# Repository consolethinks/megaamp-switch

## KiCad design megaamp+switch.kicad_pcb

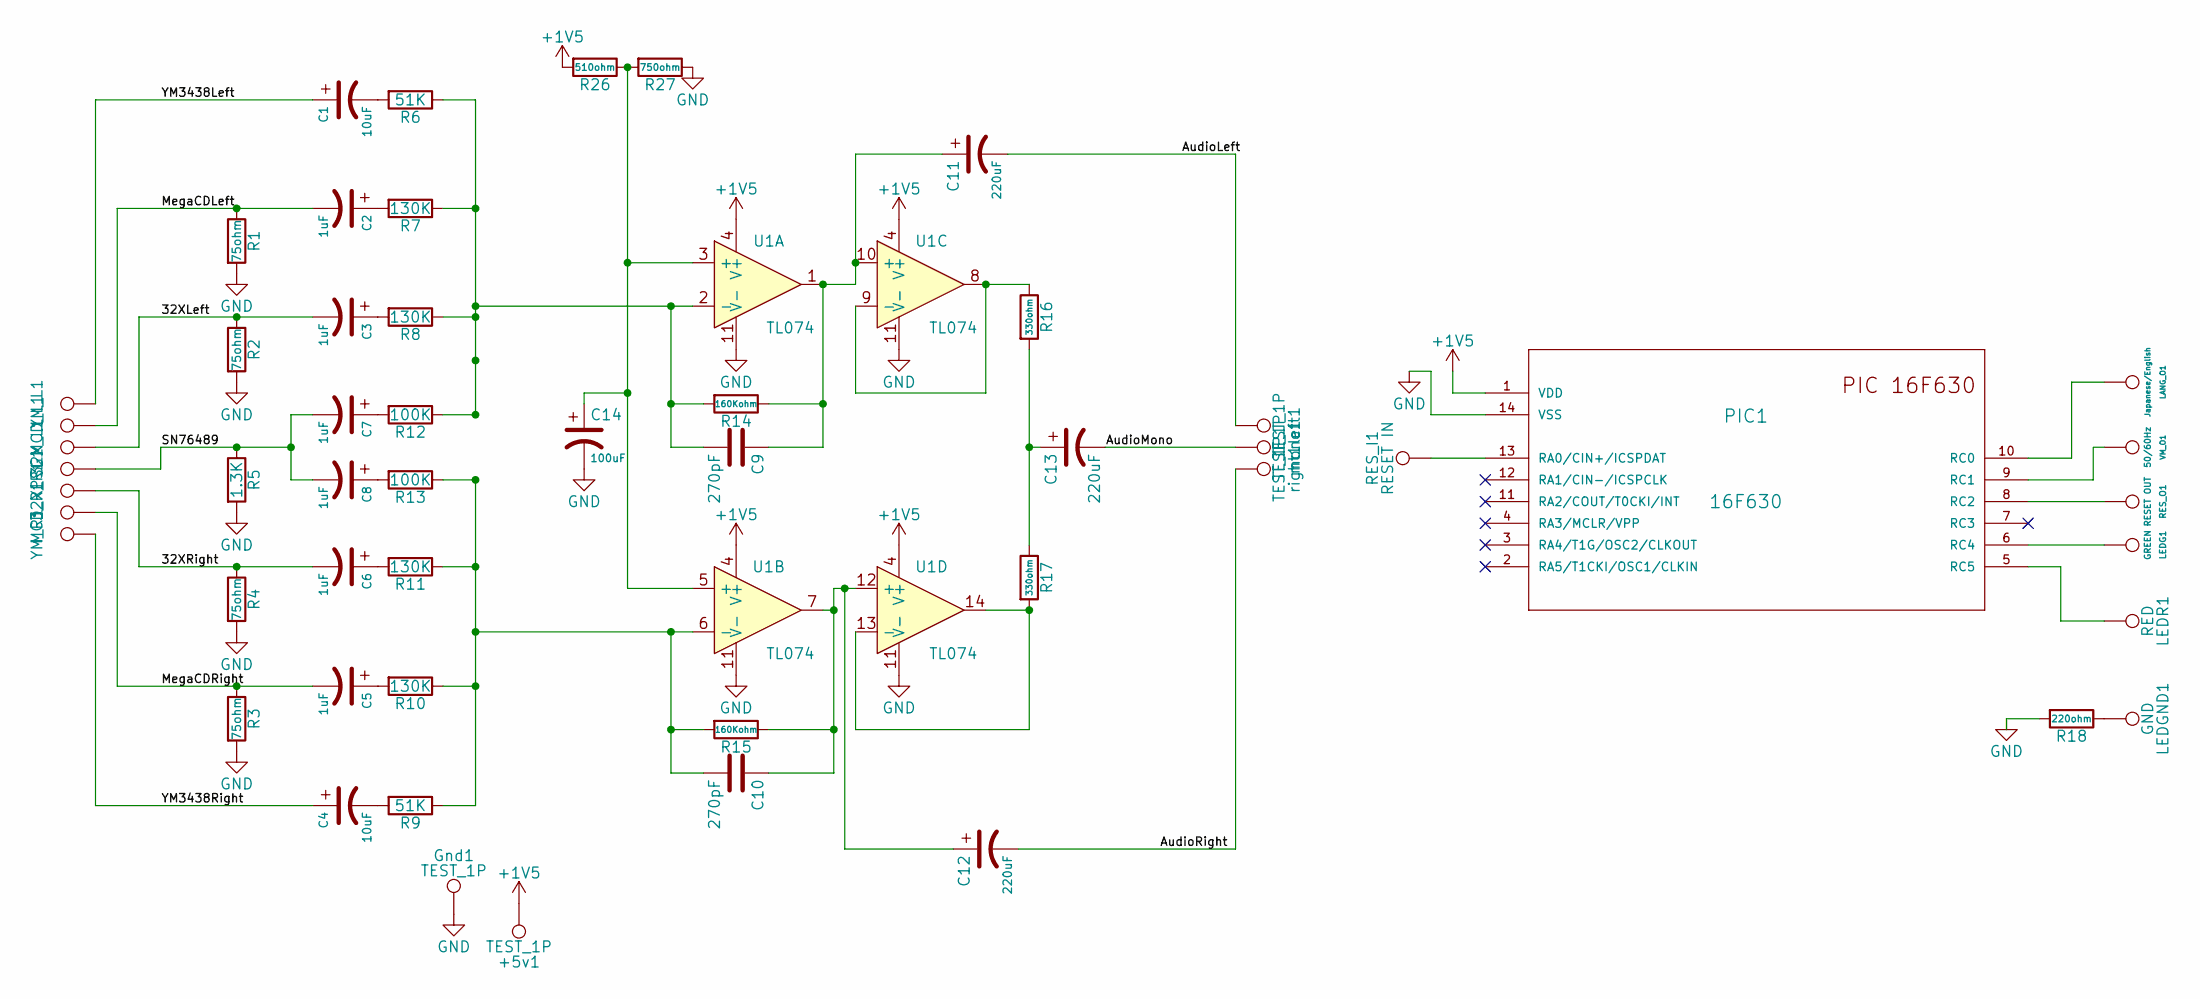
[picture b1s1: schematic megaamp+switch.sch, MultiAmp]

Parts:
32X_L1: 32X Left Channel; SolderWirePad_single_0-8mmDrill
32X_R1: 32X Right Channel; SolderWirePad_single_0-8mmDrill
+5v1: TEST_1P; SolderWirePad_single_0-8mmDrill
C1, C4: 10uF; c_elec_4x5.3
C2, C3, C5, C6, C7, C8: 1uF; c_elec_4x5.3
C9, C10: 270pF; C_Disc_D7.5_P5
C11, C12, C13: 220uF; c_elec_4x5.3
C14: 100uF; c_elec_4x5.3
Gnd1: TEST_1P; SolderWirePad_single_0-8mmDrill
LANG_O1: Japanese/English; SolderWirePad_single_0-8mmDrill
LEDG1: GREEN; SolderWirePad_single_0-8mmDrill
LEDGND1: GND; SolderWirePad_single_0-8mmDrill
LEDR1: RED; SolderWirePad_single_0-8mmDrill
MCD_L1: Mega CD Left Channel; SolderWirePad_single_0-8mmDrill
MCD_R1: Mega CD Right Channel; SolderWirePad_single_0-8mmDrill
PIC1: 16F630; DIP-14_W7.62mm
PSG1: PSG; SolderWirePad_single_0-8mmDrill
R1, R2, R3, R4: 75ohm; R_1206
R5: 1.3K; R_1206
R6, R9: 51K; R_1206
R7, R8, R10, R11: 130K; R_1206
R12, R13: 100K; R_1206
R14, R15: 160Kohm; R_1206
R16, R17: 330ohm; R_1206
R18: 220ohm; R_1206
R26: 510ohm; R_1206
R27: 750ohm; R_1206
RES_I1: RESET IN; SolderWirePad_single_0-8mmDrill
RES_O1: RESET OUT; SolderWirePad_single_0-8mmDrill
U1: TL074; SOIC-14_N
VM_O1: 50/60Hz; SolderWirePad_single_0-8mmDrill
YM_L1: Yamaha left channel; SolderWirePad_single_0-8mmDrill
YM_R1: Yamaha Right Channel; SolderWirePad_single_0-8mmDrill
left1: TEST_1P; SolderWirePad_single_0-8mmDrill
mono1: TEST_1P; SolderWirePad_single_0-8mmDrill
right1: TEST_1P; SolderWirePad_single_0-8mmDrill

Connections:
+1V5: +5v1.1, PIC1.1 (VDD), R26.2, U1.4 (V+)
/32XLeft: 32X_L1.1, C3.2, R2.1
/32XRight: 32X_R1.1, C6.2, R4.1
/AudioLeft: C11.2, left1.1
/AudioMono: C13.2, mono1.1
/AudioRight: C12.2, right1.1
/MegaCDLeft: C2.2, MCD_L1.1, R1.1
/MegaCDRight: C5.2, MCD_R1.1, R3.1
/SN76489: C7.2, C8.2, PSG1.1, R5.1
/YM3438Left: C1.1, YM_L1.1
/YM3438Right: C4.1, YM_R1.1
GND: C14.2, Gnd1.1, PIC1.14 (VSS), R1.2, R2.2, R3.2, R4.2, R5.2, R18.2, R27.1, U1.11 (V-)
unnamed: C1.2, R6.2
unnamed: C2.1, R7.2
unnamed: C3.1, R8.2
unnamed: C4.2, R9.2
unnamed: C5.1, R10.2
unnamed: C6.1, R11.2
unnamed: C7.1, R12.2
unnamed: C8.1, R13.2
unnamed: C9.2, R6.1, R7.1, R8.1, R12.1, R14.2, U1.2 (-)
unnamed: C10.1, C12.1, R15.1, U1.7, U1.12 (+)
unnamed: C10.2, R9.1, R10.1, R11.1, R13.1, R15.2, U1.6 (-)
unnamed: C9.1, C11.1, R14.1, U1.1, U1.10 (+)
unnamed: C13.1, R16.2, R17.1
unnamed: C14.1, R26.1, R27.2, U1.3 (+), U1.5 (+)
unnamed: LANG_O1.1, PIC1.10 (RC0)
unnamed: LEDG1.1, PIC1.6 (RC4)
unnamed: LEDGND1.1, R18.1
unnamed: LEDR1.1, PIC1.5 (RC5)
unnamed: PIC1.8 (RC2), RES_O1.1
unnamed: PIC1.9 (RC1), VM_O1.1
unnamed: PIC1.13 (RA0/CIN+/ICSPDAT), RES_I1.1
unnamed: R16.1, U1.8, U1.9 (-)
unnamed: R17.2, U1.13 (-), U1.14

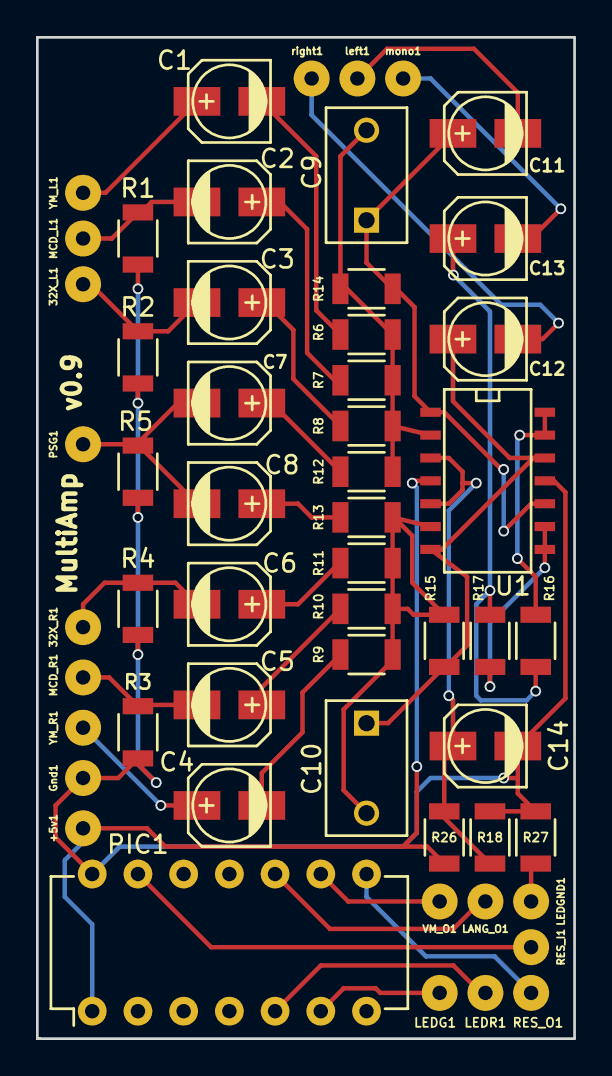
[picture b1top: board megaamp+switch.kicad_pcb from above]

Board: 2 copper layers, 29.8 x 55.6 mm, 55 parts (0 on the bottom side), 35 nets.

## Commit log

2020-08-15 Add initial files
    Added my old work directory to the repository
